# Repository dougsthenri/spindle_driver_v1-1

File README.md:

# spindle_driver Version 1.1
PCB project for a BLDC motor driver tailored for CNC spindle motors.

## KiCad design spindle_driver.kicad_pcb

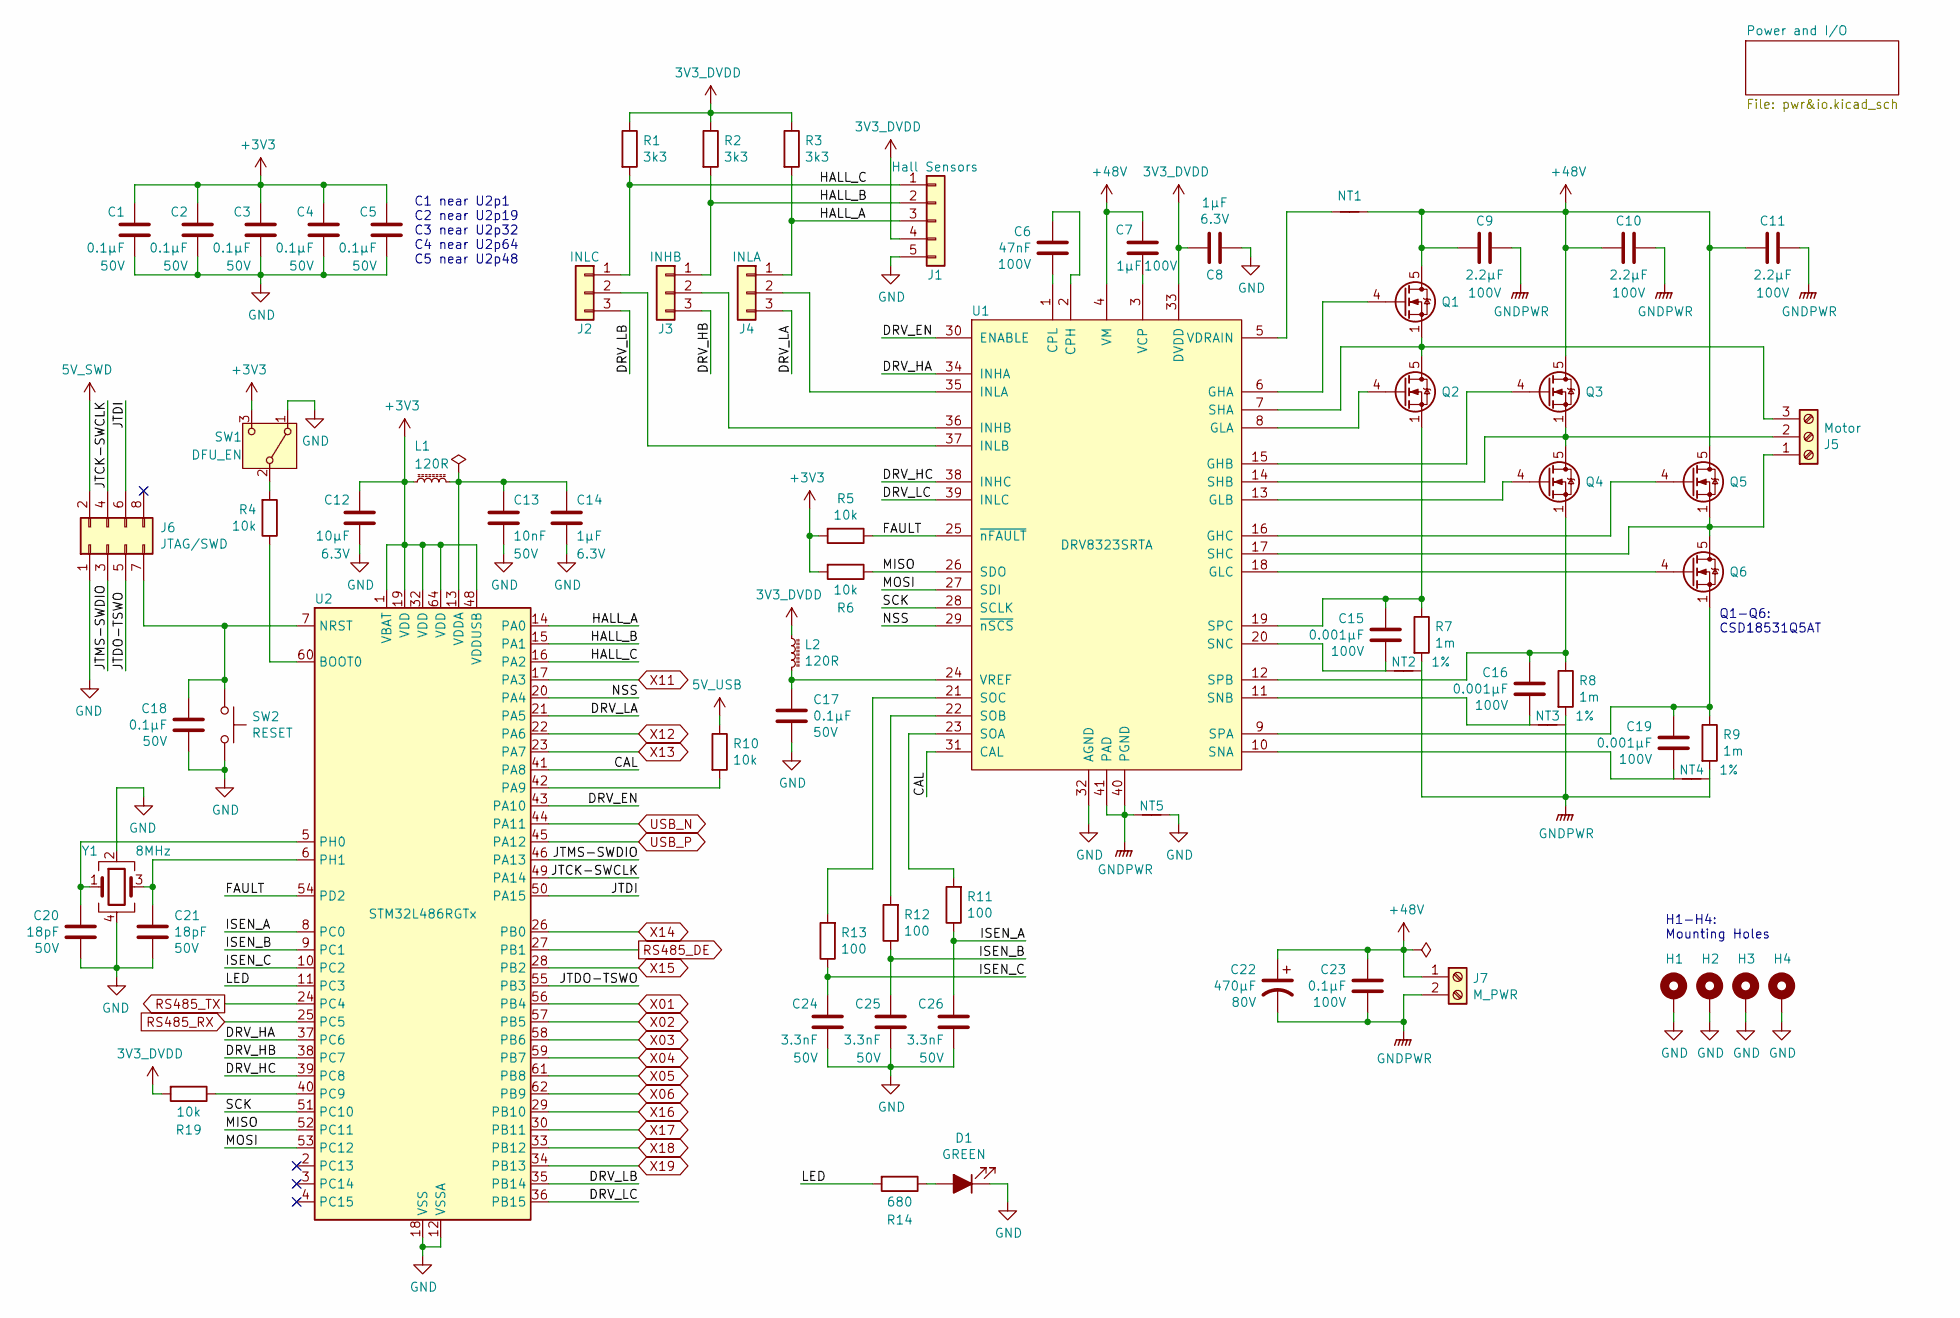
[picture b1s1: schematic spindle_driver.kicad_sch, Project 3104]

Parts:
C1, C2, C3, C4, C5, C17, C18: 0.1µF; C_0805_2012Metric; Voltage 50V; Part# C0805C104K5RACTU
C6: 47nF; C_1812_4532Metric; Voltage 100V; Part# C1812C473K1RACTU
C7: 1µF; C_1206_3216Metric; Voltage 100V; Part# CL31B105KCHNNNE
C8, C14: 1µF; C_0603_1608Metric; Voltage 6.3V; Part# CL10B105KQ8NNNC
C9, C10, C11: 2.2µF; C_1210_3225Metric; Voltage 100V; Part# 12101C225K4T2A
C12: 10µF; CP_EIA-3216-18_Kemet-A; Voltage 6.3V; Part# T491A106K006AT
C13: 10nF; C_0805_2012Metric; Voltage 50V; Part# CC0805KRX7R9BB103
C15, C16, C19: 0.001µF; C_0805_2012Metric; Voltage 100V; Part# CC0805JRX7R0BB102
C20, C21: 18pF; C_0603_1608Metric; Voltage 50V; Part# CL10C180FB8NNNC
C22: 470µF; EEU-FS1K471L; Voltage 80V; Part# EEU-FS1K471L
C23: 0.1µF; C_1206_3216Metric; Voltage 100V; Part# CC1206JKX7R0BB104
C24, C25, C26: 3.3nF; C_0805_2012Metric; Voltage 50V; Part# CL21C332JBFNNNF
D1: GREEN; LED_PLCC-2; Part# VLMC3101-GS08
H1, H2, H3, H4: MountingHole_Pad; MountingHole_3.2mm_M3_DIN965_Pad
J1: Hall Sensors; JST_XH_S5B-XH-A_1x05_P2.50mm_Horizontal_Protruded; Part# S5B-XH-A(LF)(SN)
J2: INLC; PinHeader_1x03_P2.54mm_Vertical
J3: INHB; PinHeader_1x03_P2.54mm_Vertical
J4: INLA; PinHeader_1x03_P2.54mm_Vertical
J5: Motor; PhoenixContact_MSTBA_2,5_3-G-5,08_1x03_P5.08mm_Horizontal_P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; Part# MSTBA 2.5/ 3-G-5.08
J6: JTAG/SWD; IDC-Header_2x04_P2.54mm_Vertical; Part# BHR-08-VUA
J7: M_PWR; PhoenixContact_MSTBA_2,5_2-G-5,08_1x02_P5.08mm_Horizontal; Part# MSTBA 2.5/ 2-G-5.08
L1, L2: 120R; L_0805_2012Metric; Part# MLS0805-4S7-121
NT1, NT2, NT3, NT4, NT5: Net-Tie_2; NetTie-2_SMD_Pad0.25mm
Q1, Q2, Q3, Q4, Q5, Q6: CSD18531Q5A; TDSON-8-1
R1, R2, R3: 3k3; R_0805_2012Metric; Part# CRCW08053K30JNEA
R4, R5, R6, R10, R19: 10k; R_0805_2012Metric; Part# RC0805JR-0710KL
R7, R8, R9: 1m; R_2512_6332Metric; Tolerance 1%; Part# ERJ-MS4SF1M0U
R11, R12, R13: 100; C_0805_2012Metric; Part# CRGCQ0805J100R
R14: 680; R_0805_2012Metric; Part# RC0805FR-07680RL
SW1: DFU_EN; Alps_SSSS213000; Part# SSSS213000
SW2: RESET; SW_SPST_EVQQ2; Part# EVQ-Q2Y03W
U1: DRV8323SRTA; Texas_S-PWQFN-N40; Part# DRV8323SRTAR
U2: STM32L486RGTx; LQFP-64_10x10mm_P0.5mm
Y1: 8MHz; Crystal_SMD_3225-4Pin_3.2x2.5mm; Part# 12.60028

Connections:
3V3_DVDD: C8.1, J1.4, L2.1, R1.1, R2.1, R3.1, R19.2, U1.33 (DVDD)
5V_SWD: J6.2; also elsewhere on the board
5V_USB: R10.1; also elsewhere on the board
+3V3: C1.1, C2.1, C3.1, C4.1, C5.1, C12.1, L1.1, R5.2, R6.2, SW1.3 (C), U2.1 (VBAT), U2.19 (VDD), U2.32 (VDD), U2.48 (VDDUSB), U2.64 (VDD); also elsewhere on the board
+48V: C7.1, C9.2, C10.2, C11.2, C22.1, C23.2, J7.1, NT1.2, Q1.5 (D), Q3.5 (D), Q5.5 (D), U1.4 (VM)
/CAL: U1.31 (CAL), U2.41 (PA8)
/DRV_EN: U1.30 (ENABLE), U2.43 (PA10)
/DRV_HA: U1.34 (INHA), U2.37 (PC6)
/DRV_HB: J3.3, U2.38 (PC7)
/DRV_HC: U1.38 (INHC), U2.39 (PC8)
/DRV_LA: J4.3, U2.21 (PA5)
/DRV_LB: J2.3, U2.35 (PB14)
/DRV_LC: U1.39 (INLC), U2.36 (PB15)
/FAULT: R5.1, U1.25 (~nFAULT), U2.54 (PD2)
/HALL_A: J1.3, J4.1, R3.2, U2.14 (PA0)
/HALL_B: J1.2, J3.1, R2.2, U2.15 (PA1)
/HALL_C: J1.1, J2.1, R1.2, U2.16 (PA2)
/ISEN_A: C26.1, R11.1, U2.8 (PC0)
/ISEN_B: C25.1, R12.1, U2.9 (PC1)
/ISEN_C: C24.1, R13.1, U2.10 (PC2)
/JTCK-SWCLK: J6.4, U2.49 (PA14)
/JTDI: J6.6, U2.50 (PA15)
/JTDO-TSWO: J6.5, U2.55 (PB3)
/JTMS-SWDIO: J6.3, U2.46 (PA13)
/LED: R14.2, U2.11 (PC3)
/MISO: R6.1, U1.26 (SDO), U2.52 (PC11)
/MOSI: U1.27 (SDI), U2.53 (PC12)
/NSS: U1.29 (~nSCS), U2.20 (PA4)
/SCK: U1.28 (SCLK), U2.51 (PC10)
GND: C1.2, C2.2, C3.2, C4.2, C5.2, C8.2, C12.2, C13.2, C14.2, C17.2, C18.2, C20.1, C21.1, C24.2, C25.2, C26.2, D1.1 (K), H1.1, H2.1, H3.1, H4.1, J1.5, J6.1, NT5.2, SW1.1 (A), SW2.1, U1.32 (AGND), U2.12 (VSSA), U2.18 (VSS), U2.31 (VSS), U2.47 (VSS), U2.63 (VSS), Y1.2, Y1.4; also elsewhere on the board
GNDPWR: C9.1, C10.1, C11.1, C22.2, C23.1, J7.2, NT2.2, NT3.2, NT4.2, NT5.1, R7.2, R8.2, R9.2, U1.40 (PGND), U1.41 (PAD)
unnamed: C6.1, U1.1 (CPL)
unnamed: C6.2, U1.2 (CPH)
unnamed: C7.2, U1.3 (VCP)
unnamed: C13.1, C14.1, L1.2, U2.13 (VDDA)
unnamed: C15.1, NT2.1, U1.20 (SNC)
unnamed: C15.2, Q2.1 (S), Q2.2 (S), Q2.3 (S), R7.1, U1.19 (SPC)
unnamed: C16.1, NT3.1, U1.11 (SNB)
unnamed: C16.2, Q4.1 (S), Q4.2 (S), Q4.3 (S), R8.1, U1.12 (SPB)
unnamed: C17.1, L2.2, U1.24 (VREF)
unnamed: C18.1, J6.7, SW2.2, U2.7 (NRST)
unnamed: C19.1, NT4.1, U1.10 (SNA)
unnamed: C19.2, Q6.1 (S), Q6.2 (S), Q6.3 (S), R9.1, U1.9 (SPA)
unnamed: C20.2, U2.5 (PH0), Y1.1
unnamed: C21.2, U2.6 (PH1), Y1.3
unnamed: D1.2 (A), R14.1
unnamed: J2.2, U1.37 (INLB)
unnamed: J3.2, U1.36 (INHB)
unnamed: J4.2, U1.35 (INLA)
unnamed: J5.1, Q5.1 (S), Q5.2 (S), Q5.3 (S), Q6.5 (D), U1.17 (SHC)
unnamed: J5.2, Q3.1 (S), Q3.2 (S), Q3.3 (S), Q4.5 (D), U1.14 (SHB)
unnamed: J5.3, Q1.1 (S), Q1.2 (S), Q1.3 (S), Q2.5 (D), U1.7 (SHA)
unnamed: NT1.1, U1.5 (VDRAIN)
unnamed: Q1.4 (G), U1.6 (GHA)
unnamed: Q2.4 (G), U1.8 (GLA)
unnamed: Q3.4 (G), U1.15 (GHB)
unnamed: Q4.4 (G), U1.13 (GLB)
unnamed: Q5.4 (G), U1.16 (GHC)
unnamed: Q6.4 (G), U1.18 (GLC)
unnamed: R4.1, U2.60 (BOOT0)
unnamed: R4.2, SW1.2 (B)
unnamed: R10.2, U2.42 (PA9)
unnamed: R11.2, U1.23 (SOA)
unnamed: R12.2, U1.22 (SOB)
unnamed: R13.2, U1.21 (SOC)
unnamed: R19.1, U2.40 (PC9)
RS485_DE: U2.27 (PB1); also elsewhere on the board
RS485_RX: U2.25 (PC5); also elsewhere on the board
RS485_TX: U2.24 (PC4); also elsewhere on the board
X01: U2.56 (PB4); also elsewhere on the board
X02: U2.57 (PB5); also elsewhere on the board
X03: U2.58 (PB6); also elsewhere on the board
X04: U2.59 (PB7); also elsewhere on the board
X05: U2.61 (PB8); also elsewhere on the board
X06: U2.62 (PB9); also elsewhere on the board
X11: U2.17 (PA3); also elsewhere on the board
X12: U2.22 (PA6); also elsewhere on the board
X13: U2.23 (PA7); also elsewhere on the board
X14: U2.26 (PB0); also elsewhere on the board
X15: U2.28 (PB2); also elsewhere on the board
X16: U2.29 (PB10); also elsewhere on the board
X17: U2.30 (PB11); also elsewhere on the board
X18: U2.33 (PB12); also elsewhere on the board
X19: U2.34 (PB13); also elsewhere on the board

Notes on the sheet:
C1 near U2p1 C2 near U2p19 C3 near U2p32 C4 near U2p64 C5 near U2p48
H1-H4: Mounting Holes
Q1-Q6: CSD18531Q5AT

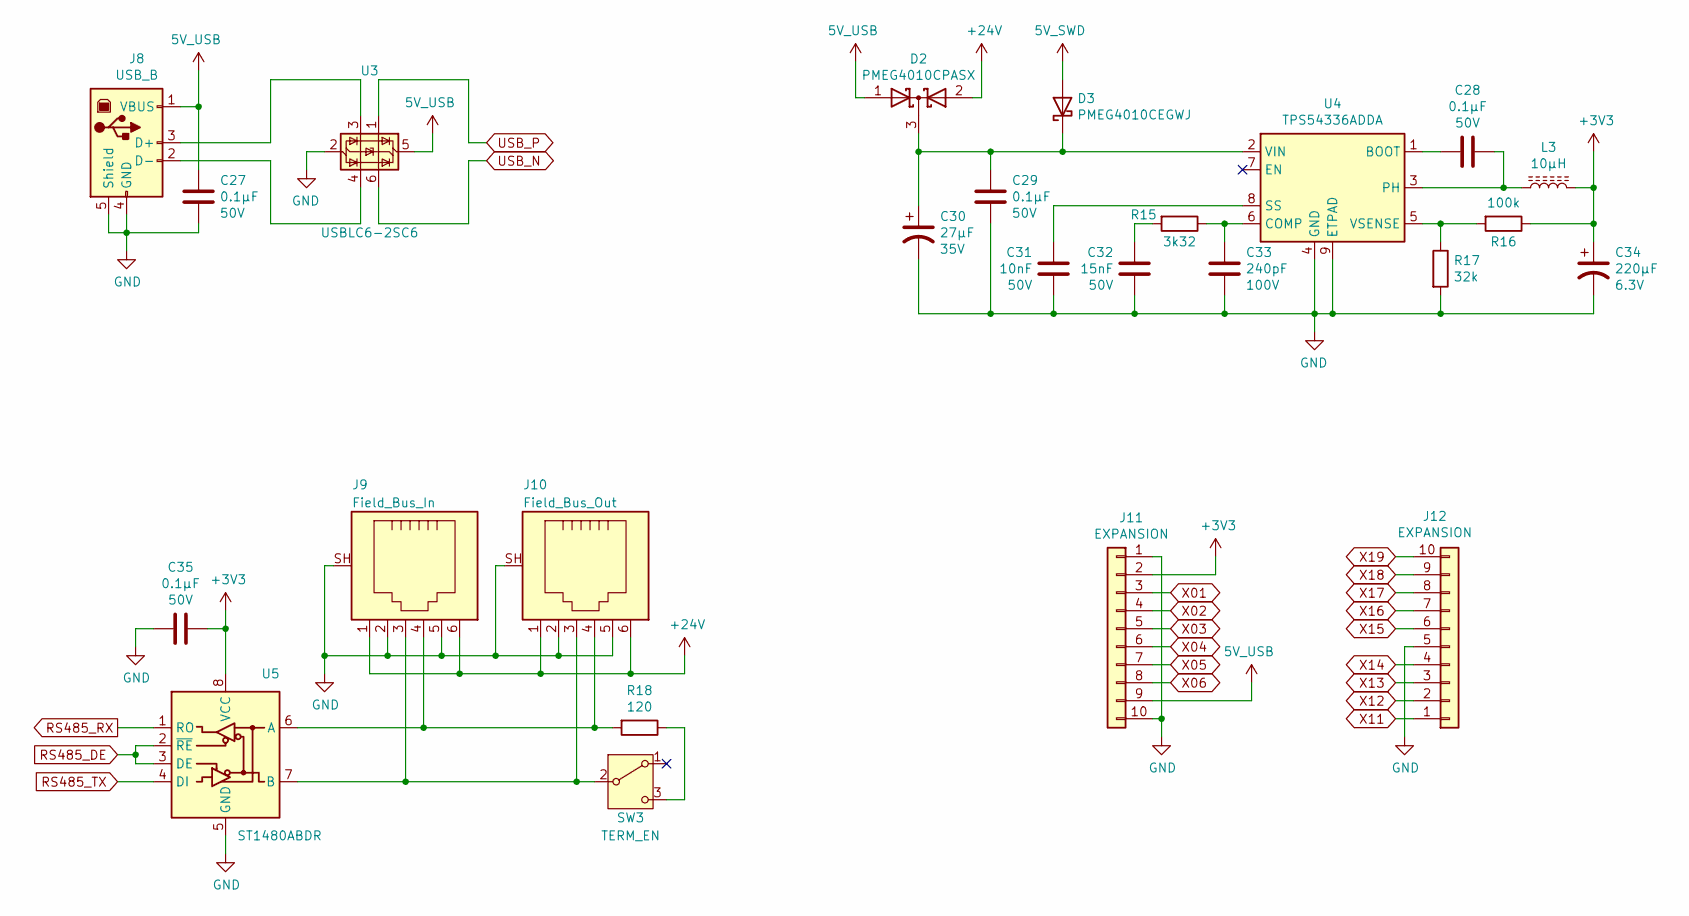
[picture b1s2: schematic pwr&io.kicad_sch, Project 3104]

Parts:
C27, C35: 0.1µF; C_0805_2012Metric; Voltage 50V; Part# C0805C104K5RACTU
C28, C29: 0.1µF; C_0805_2012Metric; Voltage 50V; Part# CC0805KRX7R9BB104
C30: 27µF; CP_Elec_6.3x5.8; Voltage 35V; Part# EEH-ZA1V270P
C31: 10nF; C_0805_2012Metric; Voltage 50V; Part# CC0805KRX7R9BB103
C32: 15nF; C_0805_2012Metric; Voltage 50V; Part# CGA4F2C0G1H153J085AA
C33: 240pF; C_0805_2012Metric; Voltage 100V; Part# GRM2165C2A241JA01D
C34: 220µF; CP_Elec_6.3x5.9; Voltage 6.3V; Part# 6SVPE220M
D2: PMEG4010CPASX; SOT1061
D3: PMEG4010CEGWJ; D_SOD-123
J8: USB_B; USB_B_Samtec_USBR-B-S-S-O-TH_Horizontal_Protruded; Part# USBR-B-S-S-O-TH
J9: Field_Bus_In; RJ12
J10: Field_Bus_Out; RJ12
J11, J12: EXPANSION; PinSocket_1x10_P2.54mm_Vertical; Part# SSW-110-01-T-S
L3: 10µH; SRN6045-100M; Part# SRN6045-100M
R15: 3k32; R_0805_2012Metric; Part# CRCW08053K32FKEA
R16: 100k; R_0805_2012Metric; Part# CRCW0805100KFKEA
R17: 32k; R_0805_2012Metric; Part# TNPW080532K0BETA
R18: 120; R_0805_2012Metric; Part# MC01W08055120R
SW3: TERM_EN; Alps_SSSS213000; Part# SSSS213000
U3: USBLC6-2SC6; SOT-23-6
U4: TPS54336ADDA; TI_SO-PowerPAD-8
U5: ST1480ABDR; SOIC-8_3.9x4.9mm_P1.27mm

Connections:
5V_SWD: D3.2 (A); also elsewhere on the board
5V_USB: C27.1, D2.1 (A), J8.1 (VBUS), J11.9, U3.5 (VBUS); also elsewhere on the board
+3V3: C34.1, C35.1, J11.2, L3.2, R16.1, U5.8 (VCC); also elsewhere on the board
+24V: D2.2 (A), J9.1, J9.6, J10.1, J10.6
GND: C27.2, C29.2, C30.2, C31.1, C32.1, C33.2, C34.2, C35.2, J8.4 (GND), J8.5 (Shield), J9.2, J9.5, J9.SH, J10.2, J10.5, J10.SH, J11.1, J11.10, J12.5, R17.2, U3.2 (GND), U4.4 (GND), U4.9 (ETPAD), U5.5 (GND); also elsewhere on the board
unnamed: C28.1, L3.1, U4.3 (PH)
unnamed: C28.2, U4.1 (BOOT)
unnamed: C29.1, C30.1, D2.3 (K), D3.1 (K), U4.2 (VIN)
unnamed: C31.2, U4.8 (SS)
unnamed: C32.2, R15.2
unnamed: C33.1, R15.1, U4.6 (COMP)
unnamed: R16.2, R17.1, U4.5 (VSENSE)
unnamed: R18.1, SW3.3 (C)
RS485_DE: U5.2 (~RE), U5.3 (DE); also elsewhere on the board
RS485_RX: U5.1 (RO); also elsewhere on the board
RS485_TX: U5.4 (DI); also elsewhere on the board
X01: J11.3; also elsewhere on the board
X02: J11.4; also elsewhere on the board
X03: J11.5; also elsewhere on the board
X04: J11.6; also elsewhere on the board
X05: J11.7; also elsewhere on the board
X06: J11.8; also elsewhere on the board
X11: J12.1; also elsewhere on the board
X12: J12.2; also elsewhere on the board
X13: J12.3; also elsewhere on the board
X14: J12.4; also elsewhere on the board
X15: J12.6; also elsewhere on the board
X16: J12.7; also elsewhere on the board
X17: J12.8; also elsewhere on the board
X18: J12.9; also elsewhere on the board
X19: J12.10; also elsewhere on the board

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
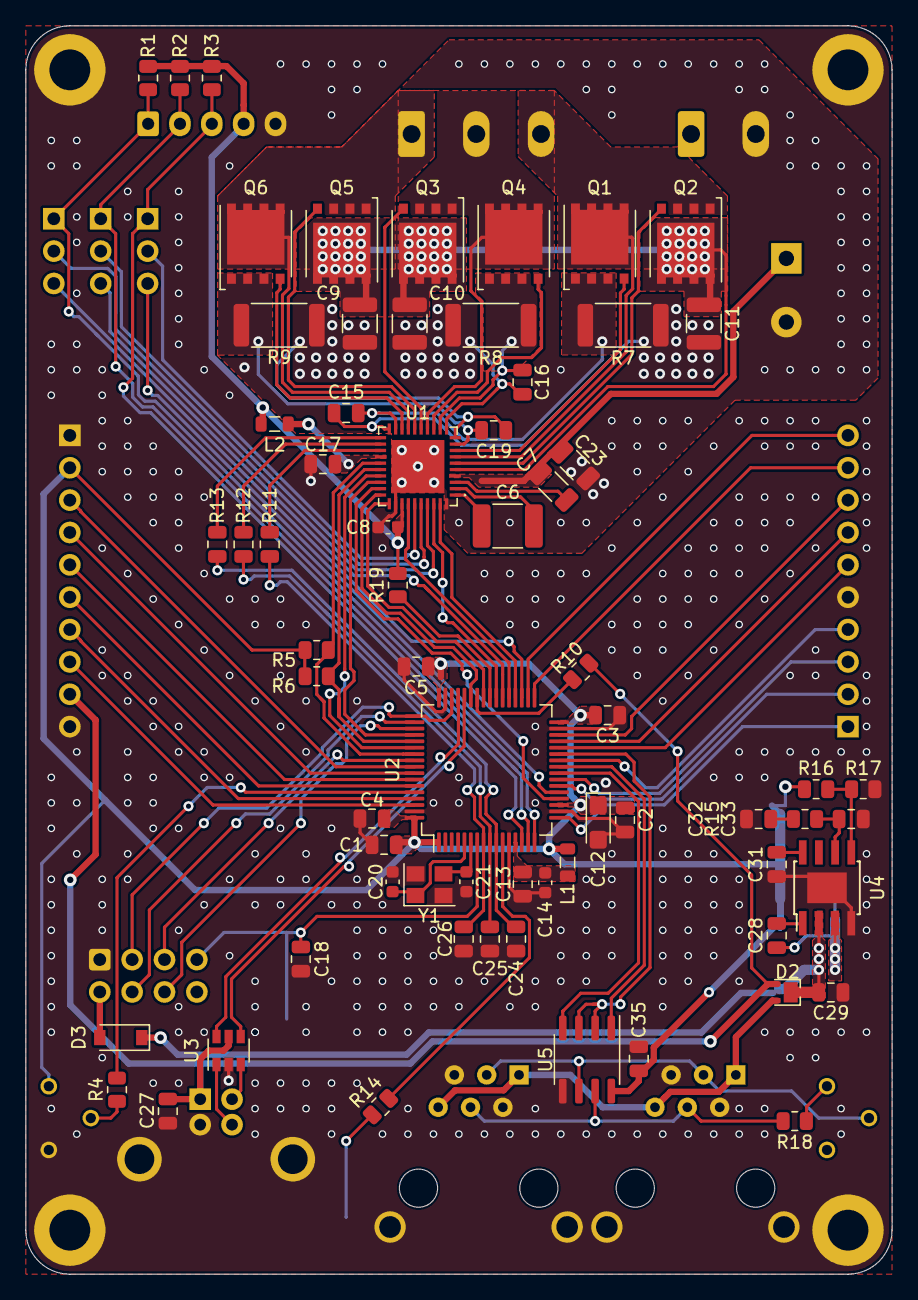
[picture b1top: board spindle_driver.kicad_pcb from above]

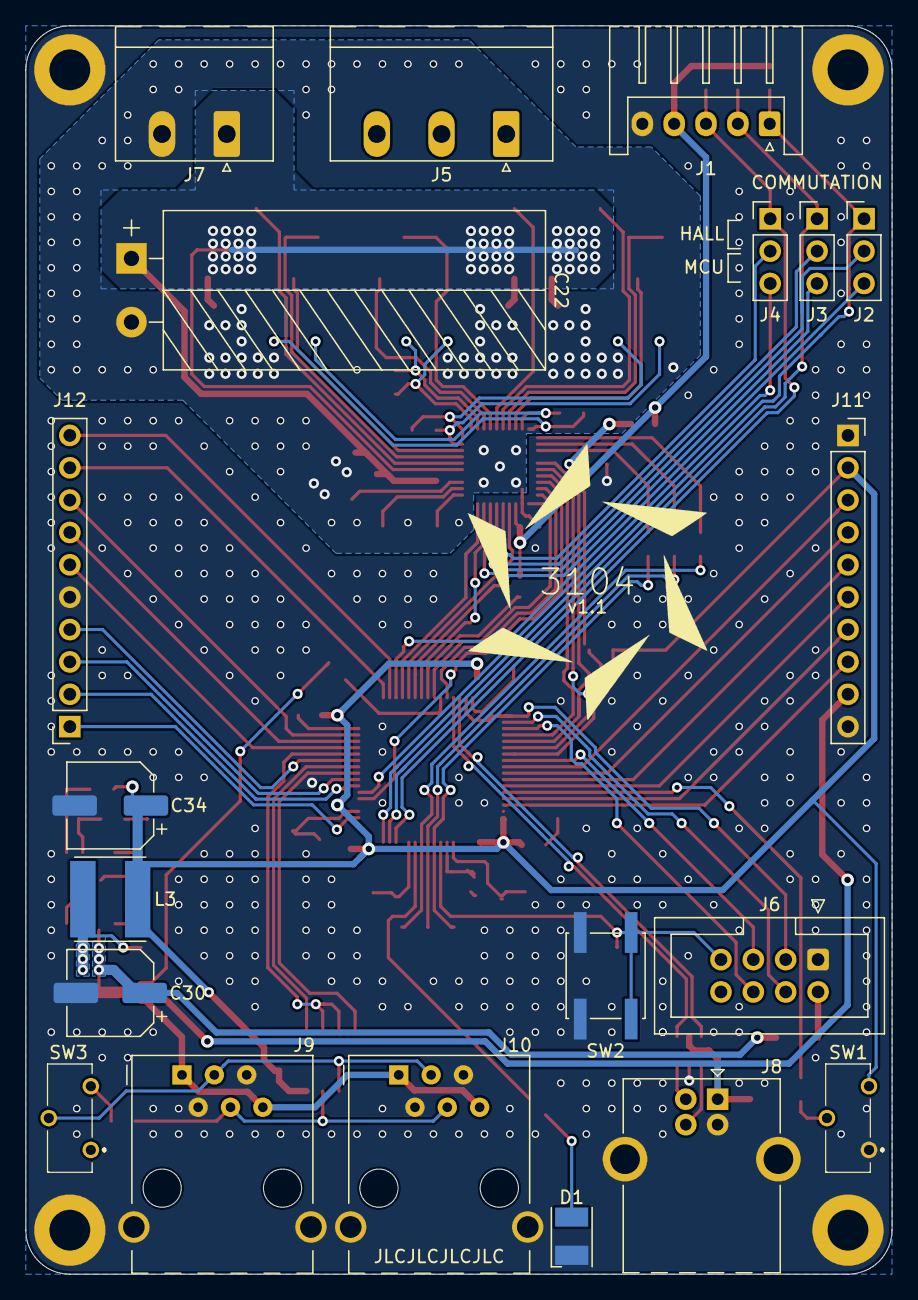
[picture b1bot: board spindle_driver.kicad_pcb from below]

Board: 2 copper layers, 68.0 x 98.0 mm, 97 parts (24 on the bottom side), 99 nets.

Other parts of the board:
G0: Project_ID_700dpi

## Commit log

2025-04-03 Updated project to Kicad 8
2025-04-03 Added project description
2025-04-03 Reestructured repository for publishing on GitHub
